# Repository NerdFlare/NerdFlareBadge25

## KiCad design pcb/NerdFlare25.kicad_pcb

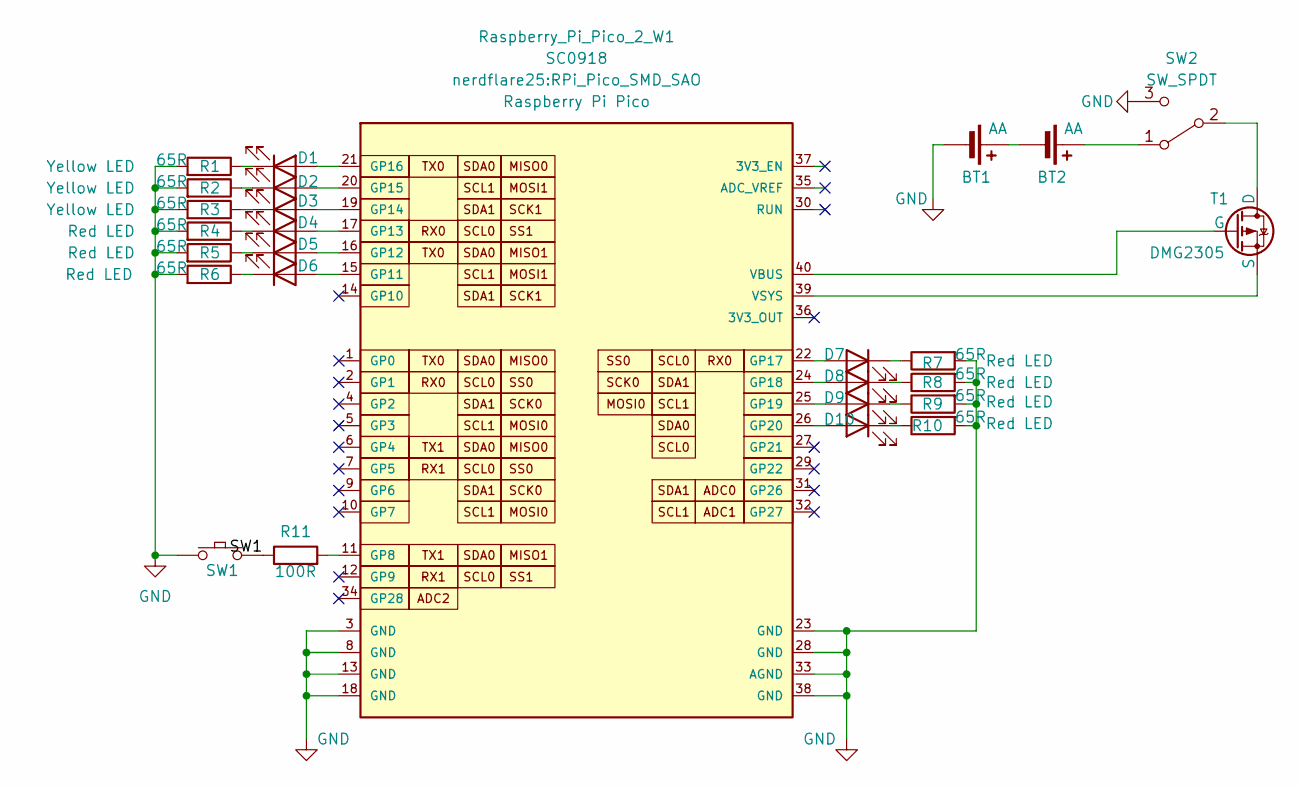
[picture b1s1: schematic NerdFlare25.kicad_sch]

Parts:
BT1, BT2: AA; BatteryHolder_Keystone_2460_1xAA_SAO
D1, D2, D3: Yellow LED; Wurth WL-SMSW Series SMT Mono-color Side view LED
D4, D5, D6, D7, D8, D9, D10: Red LED; Wurth WL-SMSW Series SMT Mono-color Side view LED
R1, R2, R3, R4, R5, R6, R7, R8, R9, R10: 65R; R_1206_3216Metric_Pad1.30x1.75mm_HandSolder
R11: 100R; R_1206_3216Metric_Pad1.30x1.75mm_HandSolder
Raspberry_Pi_Pico_2_W1: SC0918; RPi_Pico_SMD_SAO; PARTREV 1.6
SW1: SW_Push; SW_SPST_PTS645_SAO
SW2: SW_SPDT; SW_SPDT_PCM12
T1: DMG2305; SOT-23_SAO

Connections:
/SW1: R11.1, SW1.2; also elsewhere on the board
GND: BT1.2 (-), R1.2, R2.2, R3.2, R4.2, R5.2, R6.2, R7.2, R8.2, R9.2, R10.2, Raspberry_Pi_Pico_2_W1.3 (GND), Raspberry_Pi_Pico_2_W1.8 (GND), Raspberry_Pi_Pico_2_W1.13 (GND), Raspberry_Pi_Pico_2_W1.18 (GND), Raspberry_Pi_Pico_2_W1.23 (GND), Raspberry_Pi_Pico_2_W1.28 (GND), Raspberry_Pi_Pico_2_W1.33 (AGND), Raspberry_Pi_Pico_2_W1.38 (GND), SW1.1, SW2.3 (C); also elsewhere on the board
unnamed 3: D6.2 (A), Raspberry_Pi_Pico_2_W1.15 (GP11); also elsewhere on the board
unnamed 4: D5.2 (A), Raspberry_Pi_Pico_2_W1.16 (GP12); also elsewhere on the board
unnamed 5: D4.2 (A), Raspberry_Pi_Pico_2_W1.17 (GP13); also elsewhere on the board
unnamed 6: D3.2 (A), Raspberry_Pi_Pico_2_W1.19 (GP14); also elsewhere on the board
unnamed 7: D2.2 (A), Raspberry_Pi_Pico_2_W1.20 (GP15); also elsewhere on the board
unnamed 8: D1.2 (A), Raspberry_Pi_Pico_2_W1.21 (GP16); also elsewhere on the board
unnamed 9: D7.2 (A), Raspberry_Pi_Pico_2_W1.22 (GP17); also elsewhere on the board
unnamed 10: D8.2 (A), Raspberry_Pi_Pico_2_W1.24 (GP18); also elsewhere on the board
unnamed 11: D9.2 (A), Raspberry_Pi_Pico_2_W1.25 (GP19); also elsewhere on the board
unnamed 12: D10.2 (A), Raspberry_Pi_Pico_2_W1.26 (GP20); also elsewhere on the board
unnamed 13: Raspberry_Pi_Pico_2_W1.40 (VBUS), T1.1 (G); also elsewhere on the board
unnamed 14: Raspberry_Pi_Pico_2_W1.39 (VSYS), T1.2 (S); also elsewhere on the board
unnamed: BT1.1 (+), BT2.2 (-)
unnamed: BT2.1 (+), SW2.1 (A)
unnamed: D1.1 (K), R1.1
unnamed: D2.1 (K), R2.1
unnamed: D3.1 (K), R3.1
unnamed: D4.1 (K), R4.1
unnamed: D5.1 (K), R5.1
unnamed: D6.1 (K), R6.1
unnamed: D7.1 (K), R7.1
unnamed: D8.1 (K), R8.1
unnamed: D9.1 (K), R9.1
unnamed: D10.1 (K), R10.1
unnamed: R11.2, Raspberry_Pi_Pico_2_W1.11 (GP8)
unnamed: SW2.2 (B), T1.3 (D)

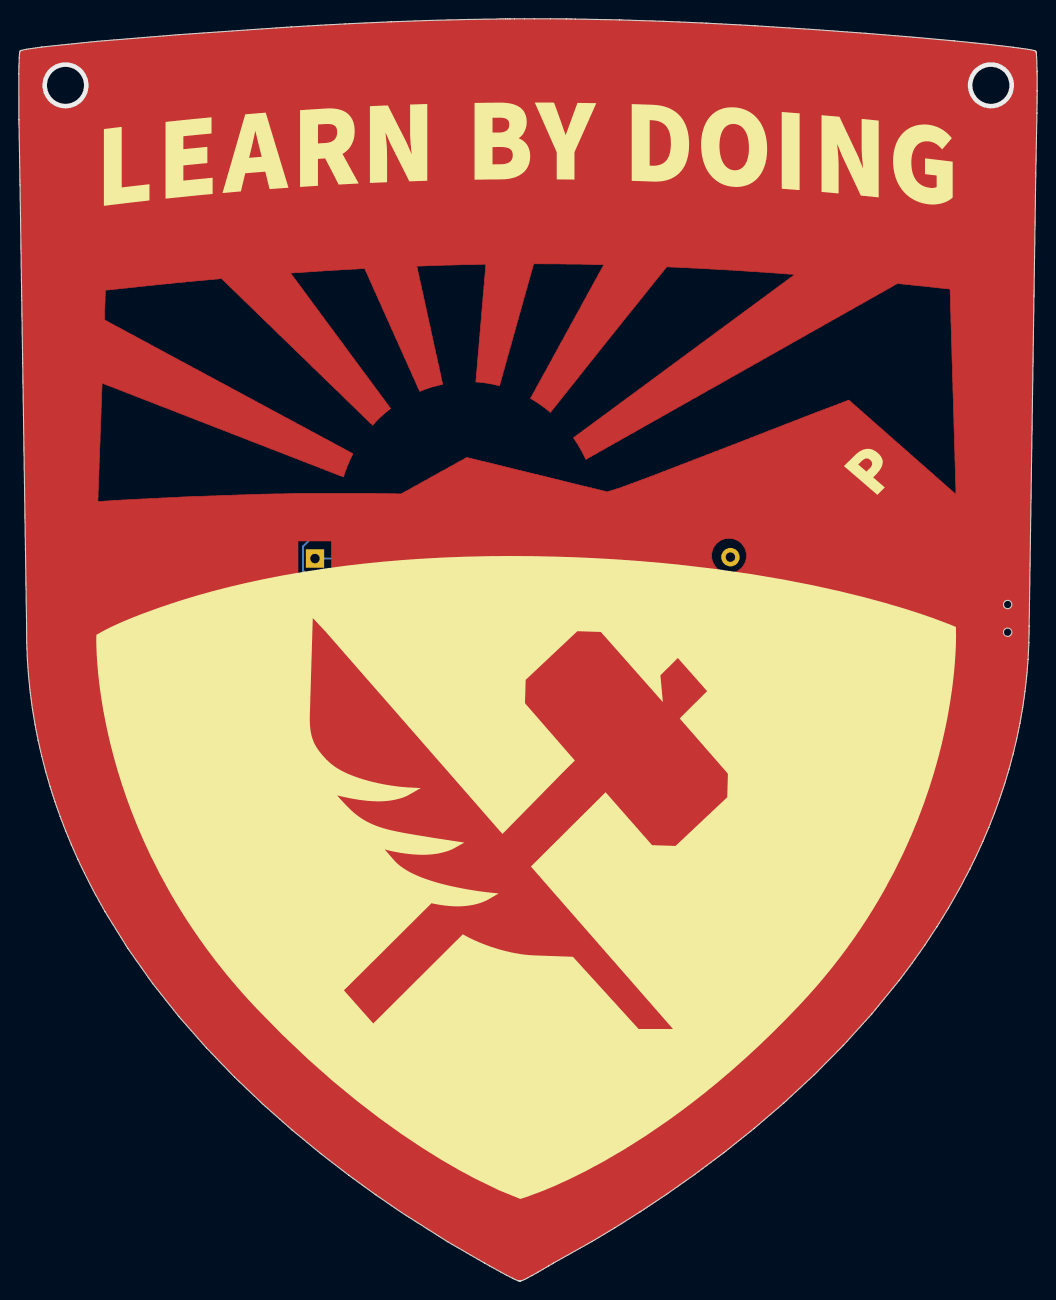
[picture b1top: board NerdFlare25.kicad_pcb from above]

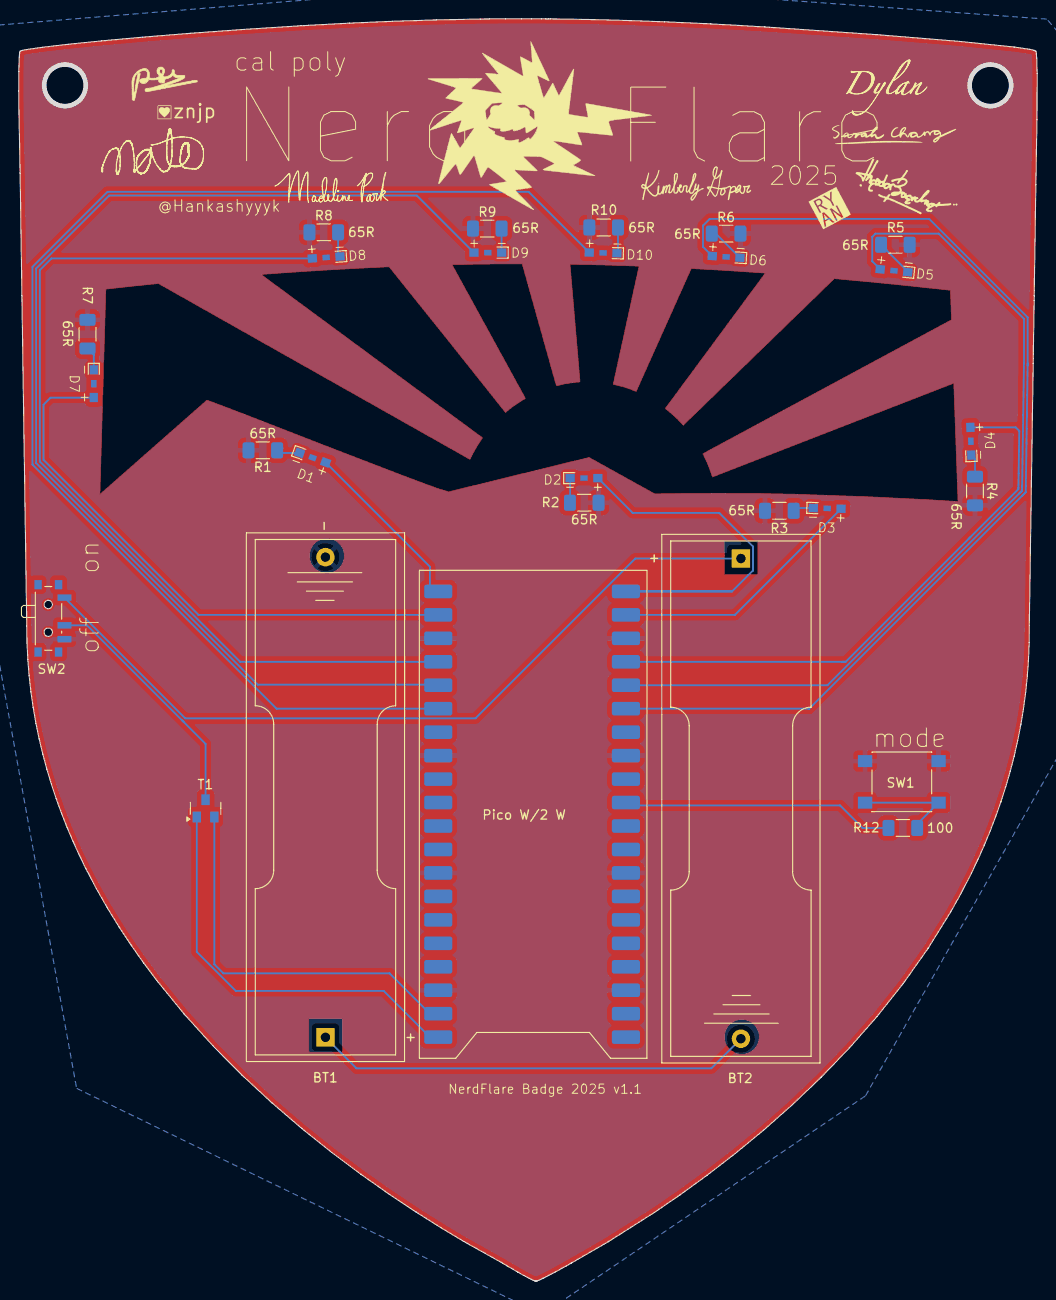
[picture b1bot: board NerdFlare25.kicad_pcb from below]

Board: 2 copper layers, 110.3 x 136.7 mm, 27 parts (27 on the bottom side), 28 nets.

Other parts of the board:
Pico W/2 W: SC0918; RPi_Pico_SMD_SAO
R12: 100; R_1206_3216Metric_Pad1.30x1.75mm_HandSolder

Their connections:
/SW1: R12.1; also elsewhere on the board
GND: Pico W/2 W.3 (GND), Pico W/2 W.8 (GND), Pico W/2 W.13 (GND), Pico W/2 W.18 (GND), Pico W/2 W.23 (GND), Pico W/2 W.28 (GND), Pico W/2 W.33 (AGND), Pico W/2 W.38 (GND); also elsewhere on the board
unnamed: Pico W/2 W.11 (GP8), R12.2
unnamed 3: Pico W/2 W.15 (GP11); also elsewhere on the board
unnamed 4: Pico W/2 W.16 (GP12); also elsewhere on the board
unnamed 5: Pico W/2 W.17 (GP13); also elsewhere on the board
unnamed 6: Pico W/2 W.19 (GP14); also elsewhere on the board
unnamed 7: Pico W/2 W.20 (GP15); also elsewhere on the board
unnamed 8: Pico W/2 W.21 (GP16); also elsewhere on the board
unnamed 9: Pico W/2 W.22 (GP17); also elsewhere on the board
unnamed 10: Pico W/2 W.24 (GP18); also elsewhere on the board
unnamed 11: Pico W/2 W.25 (GP19); also elsewhere on the board
unnamed 12: Pico W/2 W.26 (GP20); also elsewhere on the board
unnamed 13: Pico W/2 W.40 (VBUS); also elsewhere on the board
unnamed 14: Pico W/2 W.39 (VSYS); also elsewhere on the board

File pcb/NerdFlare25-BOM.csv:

NerdFlare25-BOM
Reference,Value,Datasheet,Footprint,Qty,Supplier and Ref,Price (@ 50),Cost,Notes
"BT1,BT2",AA,https://www.keyelco.com/userAssets/file/M65p28.pdf,nerdflare25:BatteryHolder_Keystone_2460_1xAA_SAO,2,https://www.digikey.com/en/products/detail/keystone-electron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,$1.11,$2.22,This has a huge lead time at DigiKey; suggested replacement requires different footprint
"D4,D5,D6,D7,D8,D9,D10",Red LED,https://www.we-online.com/components/products/datasheet/1551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,nerdflare25:Wurth WL-SMSW Series SMT Mono-color Side view LED,7,https://www.digikey.com/en/products/detail/würth-elektronik/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,$0.17,$1.18,
"D1,D2,D3",Yellow LED,,,3,,,,
"R1,R2,R3,R4,R5,R6,R7,R8,R9,R10",65R,~,Resistor_SMD:R_1206_3216Metric_Pad1.30x1.75mm_HandSolder,10,https://www.digikey.com/en/products/detail/stackpole-electro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,$0.01,$0.10,
,,,,,,,,
R11,100R,~,Resistor_SMD:R_1206_3216Metric_Pad1.30x1.75mm_HandSolder,1,,$0.01,$0.01,
Raspberry_Pi_Pico_2_W?,SC0918,https://datasheets.raspberrypi.com/picow/pico-2-w-datasheet.pdf,nerdflare25:RPi_Pico_SMD_SAO,1,https://www.digikey.com/en/products/detail/raspberry-pi/SC09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,$6.00,$6.00,
SW1,SW_Push,~,nerdflare25:SW_SPST_PTS645_SAO,1,https://www.digikey.com/en/products/detail/c-k/PTS645SM43SMT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,$0.25,$0.25,
SW2,SW_SPDT,~,Button_Switch_SMD:SW_SPDT_PCM12,1,https://www.digikey.com/en/products/detail/c-k/PCM12SMTR/1640112,$0.90,$0.90,These are currently out of stock at DigiKey and require 10 weeks of lead.
T1,DMG2305,https://www.diodes.com/assets/Datasheets/DMG2305UX.pdf,nerdflare25:SOT-23_SAO,1,https://www.digikey.com/en/products/detail/diodes-incorporat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,$0.14,$0.14,
Total,,,,,,,$10.80,

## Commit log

2025-01-16 Initial commit of the NerdFlare badge for 24-25. This is just a potential starting schematic.
2025-02-22 An initial board design and layout; added a symbol library for the badge; added symbol, footprint, and 3D model for Wurth side fire LED
2025-02-23 Moved some silk labels around.
2025-02-28 This is v0; going to fab.
2025-03-14 This is prototype v0, sent to manufactuer.
2025-03-18 This is v1 sent to production at JLCPCB; removed status LED, determined final LED colors; added silkscreen sigantures.
2025-03-19 v1.1 flipped on the on/off switch label loll
2025-03-22 Reorganized folders, added source code, and svgs. Added paste layer to Pico footprint.
2025-03-24 Commiting firmware version 1.0 - many comments added.
2025-03-27 Version 1.1; added a little more debuging messages; fixed a bug when passing the number of seen badges to randomBlink()
2025-04-05 assembly guide initial
2025-04-11 Version 1.2.1: Added a pulse mode (which is now default); users can get out of BLE blinky mode by pressing button; changed the BLE scan to not be active, which may slow things down.
